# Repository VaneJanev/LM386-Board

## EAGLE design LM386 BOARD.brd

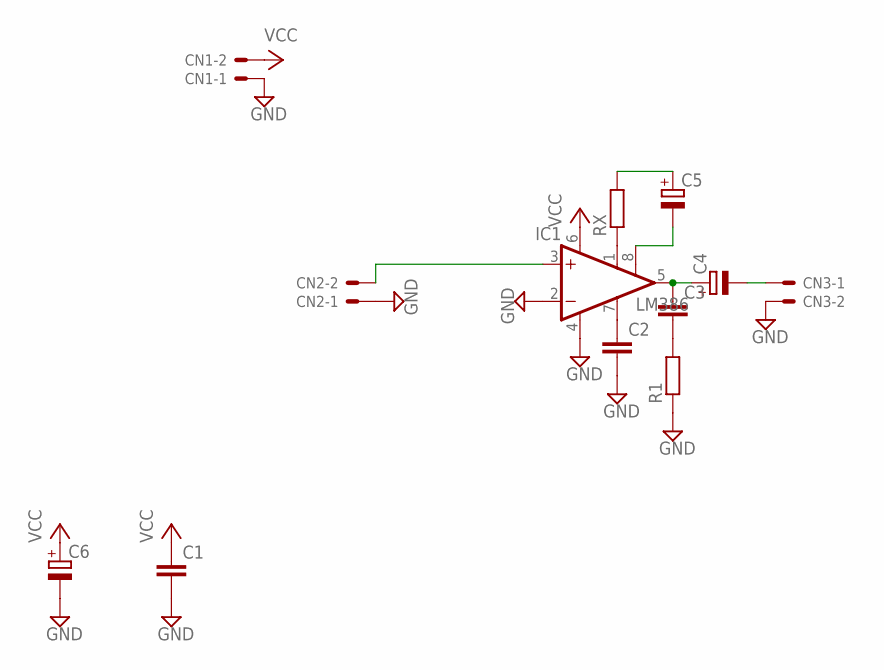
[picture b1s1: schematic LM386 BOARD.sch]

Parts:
C1, C2, C3: C-EUC0402K; C0402K
C4, C5, C6: CPOL-EU153CLV-0505; 153CLV-0505
CN1, CN2, CN3: 22-23-2021
IC1: LM386; SO08
R1: R-EU_R0805; R0805
RX: R-EU_R0805; R0805

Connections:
GND: C1.2, C2.2, C6.-, CN1.1, CN2.1, CN3.2, IC1.2 (-IN), IC1.4 (GND), R1.1
unnamed: CN2.2, IC1.3 (+IN)
unnamed: C5.-, IC1.8 (GAIN)
unnamed: IC1.1 (GAIN), RX.1
unnamed: C5.+, RX.2
unnamed: C2.1, IC1.7 (BYPASS)
unnamed: C3.1, C4.+, IC1.5 (OUT)
unnamed: C3.2, R1.2
unnamed: C4.-, CN3.1
VCC: C1.1, C6.+, CN1.2, IC1.6 (VS)

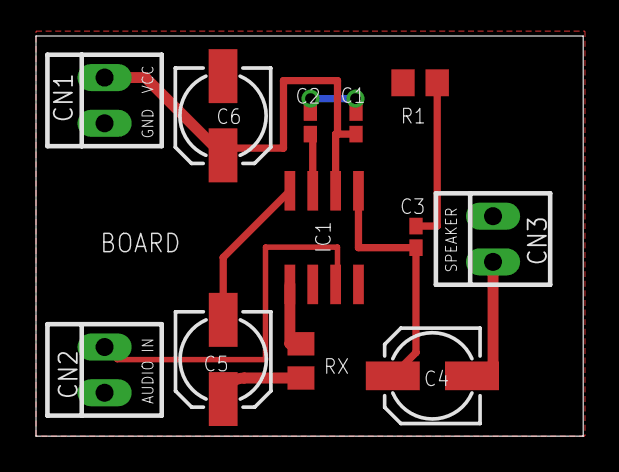
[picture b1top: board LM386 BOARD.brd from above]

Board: 2 copper layers, 30.4 x 22.2 mm, 12 parts (0 on the bottom side), 10 nets.

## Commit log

2015-06-03 :boom::camel: Added .gitattributes
2015-06-03 LM386-Board
    Eagle Design
